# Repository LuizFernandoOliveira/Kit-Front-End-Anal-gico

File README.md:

# Kit Front-End Analógico

## Descrição
Kit didático completo de Front-End para circuitos analógicos. Este kit é perfeito para se ter na bancada, pois possui diversas funcionalidades úteis durante o desenvolvimente de sistemas microcontrolados e IoT.

---

## Descrições técnicas

- Possui LDOs de 3V3 e 5V;
- Conectores USB tipo-C e Jack para alimentação do circuito;
- Possui AmpOp Full Diferencial;
- Possui ADC Full Diferencial:
- Possui Filtro ativo de 2ª Oedem Passa-altas, Passa-baixas, Passa-faixas, Rejeita-faixas;
- Possui Filtros passivos;
- Possui Buffer;
- Possui AmpOp de instrumentação;
- Possui divisores de tensão;
- Possui resistores de Pull-Up e/ou Pull-Down;
- Possui AmpOp RRIO, Ultra-Low Power, Ultra-Low Noise Não Inversor, Inversor, Integrador, Diferenciador;
- Possui chaves analogicas;
- Possui chaves digitais;
- Possui botões e LEDS;
- Possui sensores analógicos;
- Possui diodos Schotky;
- Possui diversas tensões de referência;
- Possui diversos charge pumps.

---

## Estrutura do repositório
Os arquivos de hardware foram desenvolvidos utilizando o KiCad 9.0.
- **`.kicad_pcb`**: Layout da placa de circuito impresso (Board).
- **`.kicad_sch`**: Esquemático eletrônico do sistema (Schematic).
- **`.kicad_pro`**: Gerenciador de projeto do KiCad (Project).

---

## Autor
**Dr. Luiz Fernando Pinto de Oliveira**

*Engenheiro Eletrônico especializado em Sistemas Embarcados e Ultra-Low Power.*
- **Website:** [FAPLO](https://faplo.webnode.page/)
- **LinkedIn:** [lfpo](https://www.linkedin.com/in/lfpo/)

---

Shield: [![CC BY-NC-ND 4.0][cc-by-nc-nd-shield]][cc-by-nc-nd]

This work is licensed under a
[Creative Commons Attribution-NonCommercial-NoDerivs 4.0 International License][cc-by-nc-nd].

[![CC BY-NC-ND 4.0][cc-by-nc-nd-image]][cc-by-nc-nd]

[cc-by-nc-nd]: http://creativecommons.org/licenses/by-nc-nd/4.0/
[cc-by-nc-nd-image]: https://licensebuttons.net/l/by-nc-nd/4.0/88x31.png
[cc-by-nc-nd-shield]: https://img.shields.io/badge/License-CC%20BY--NC--ND%204.0-lightgrey.svg

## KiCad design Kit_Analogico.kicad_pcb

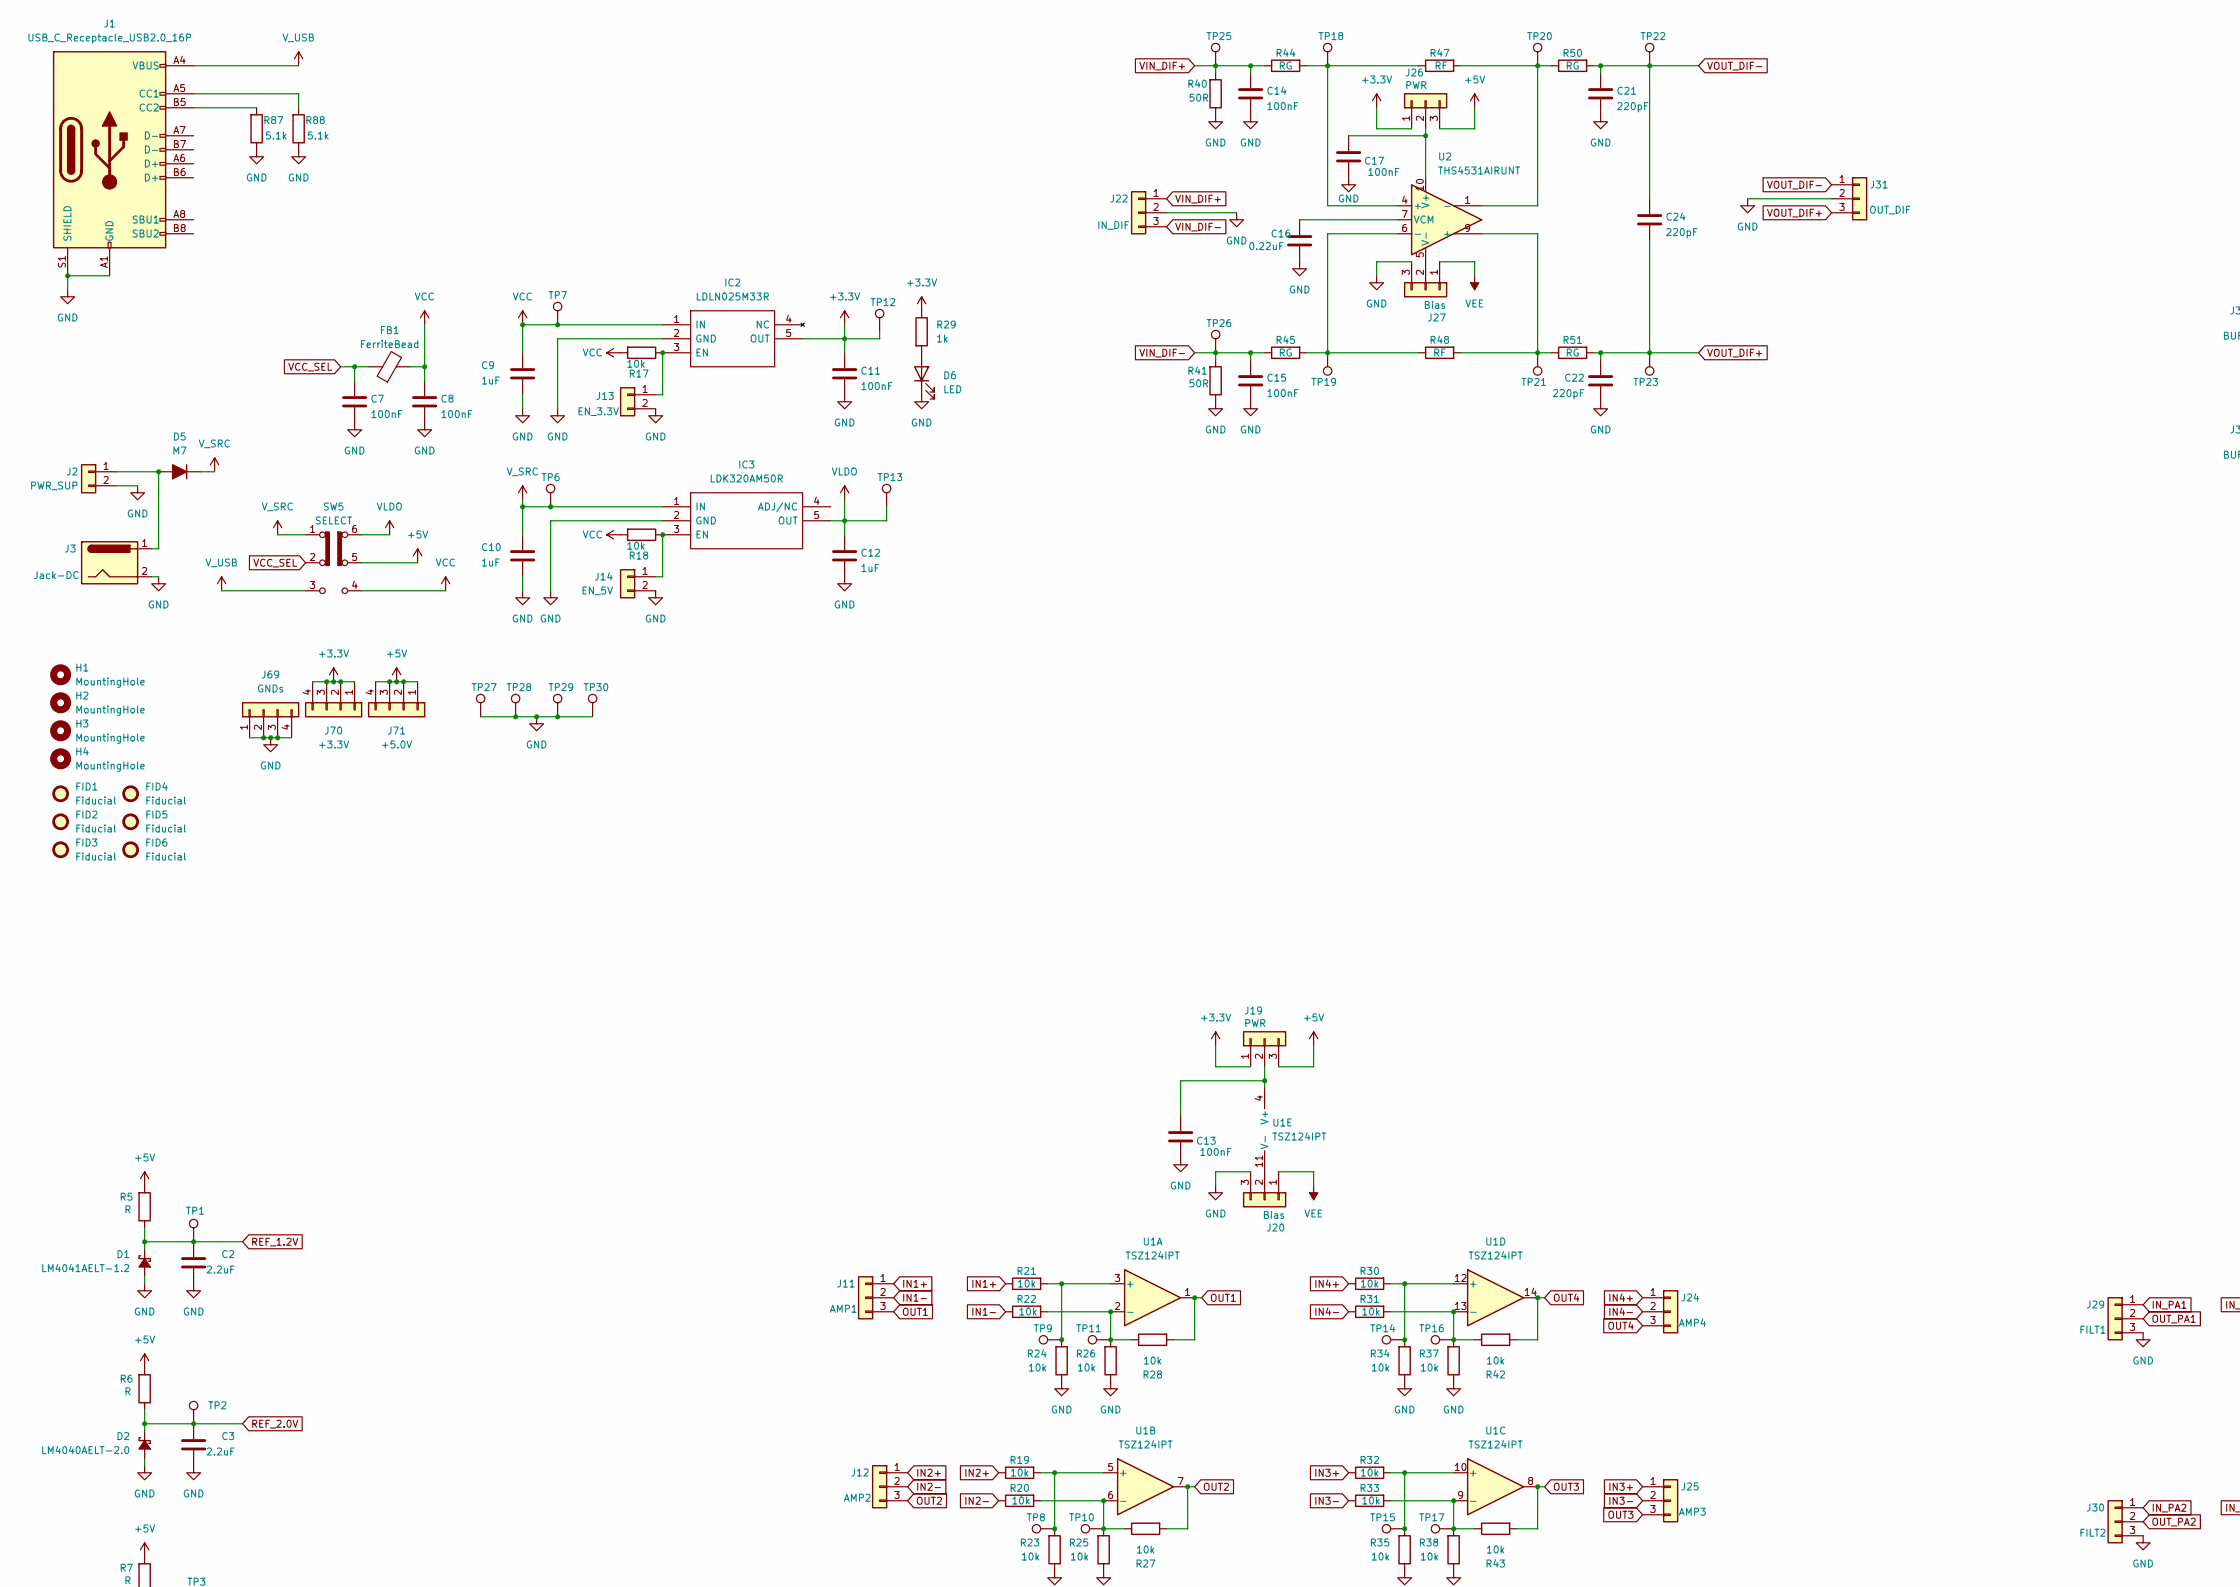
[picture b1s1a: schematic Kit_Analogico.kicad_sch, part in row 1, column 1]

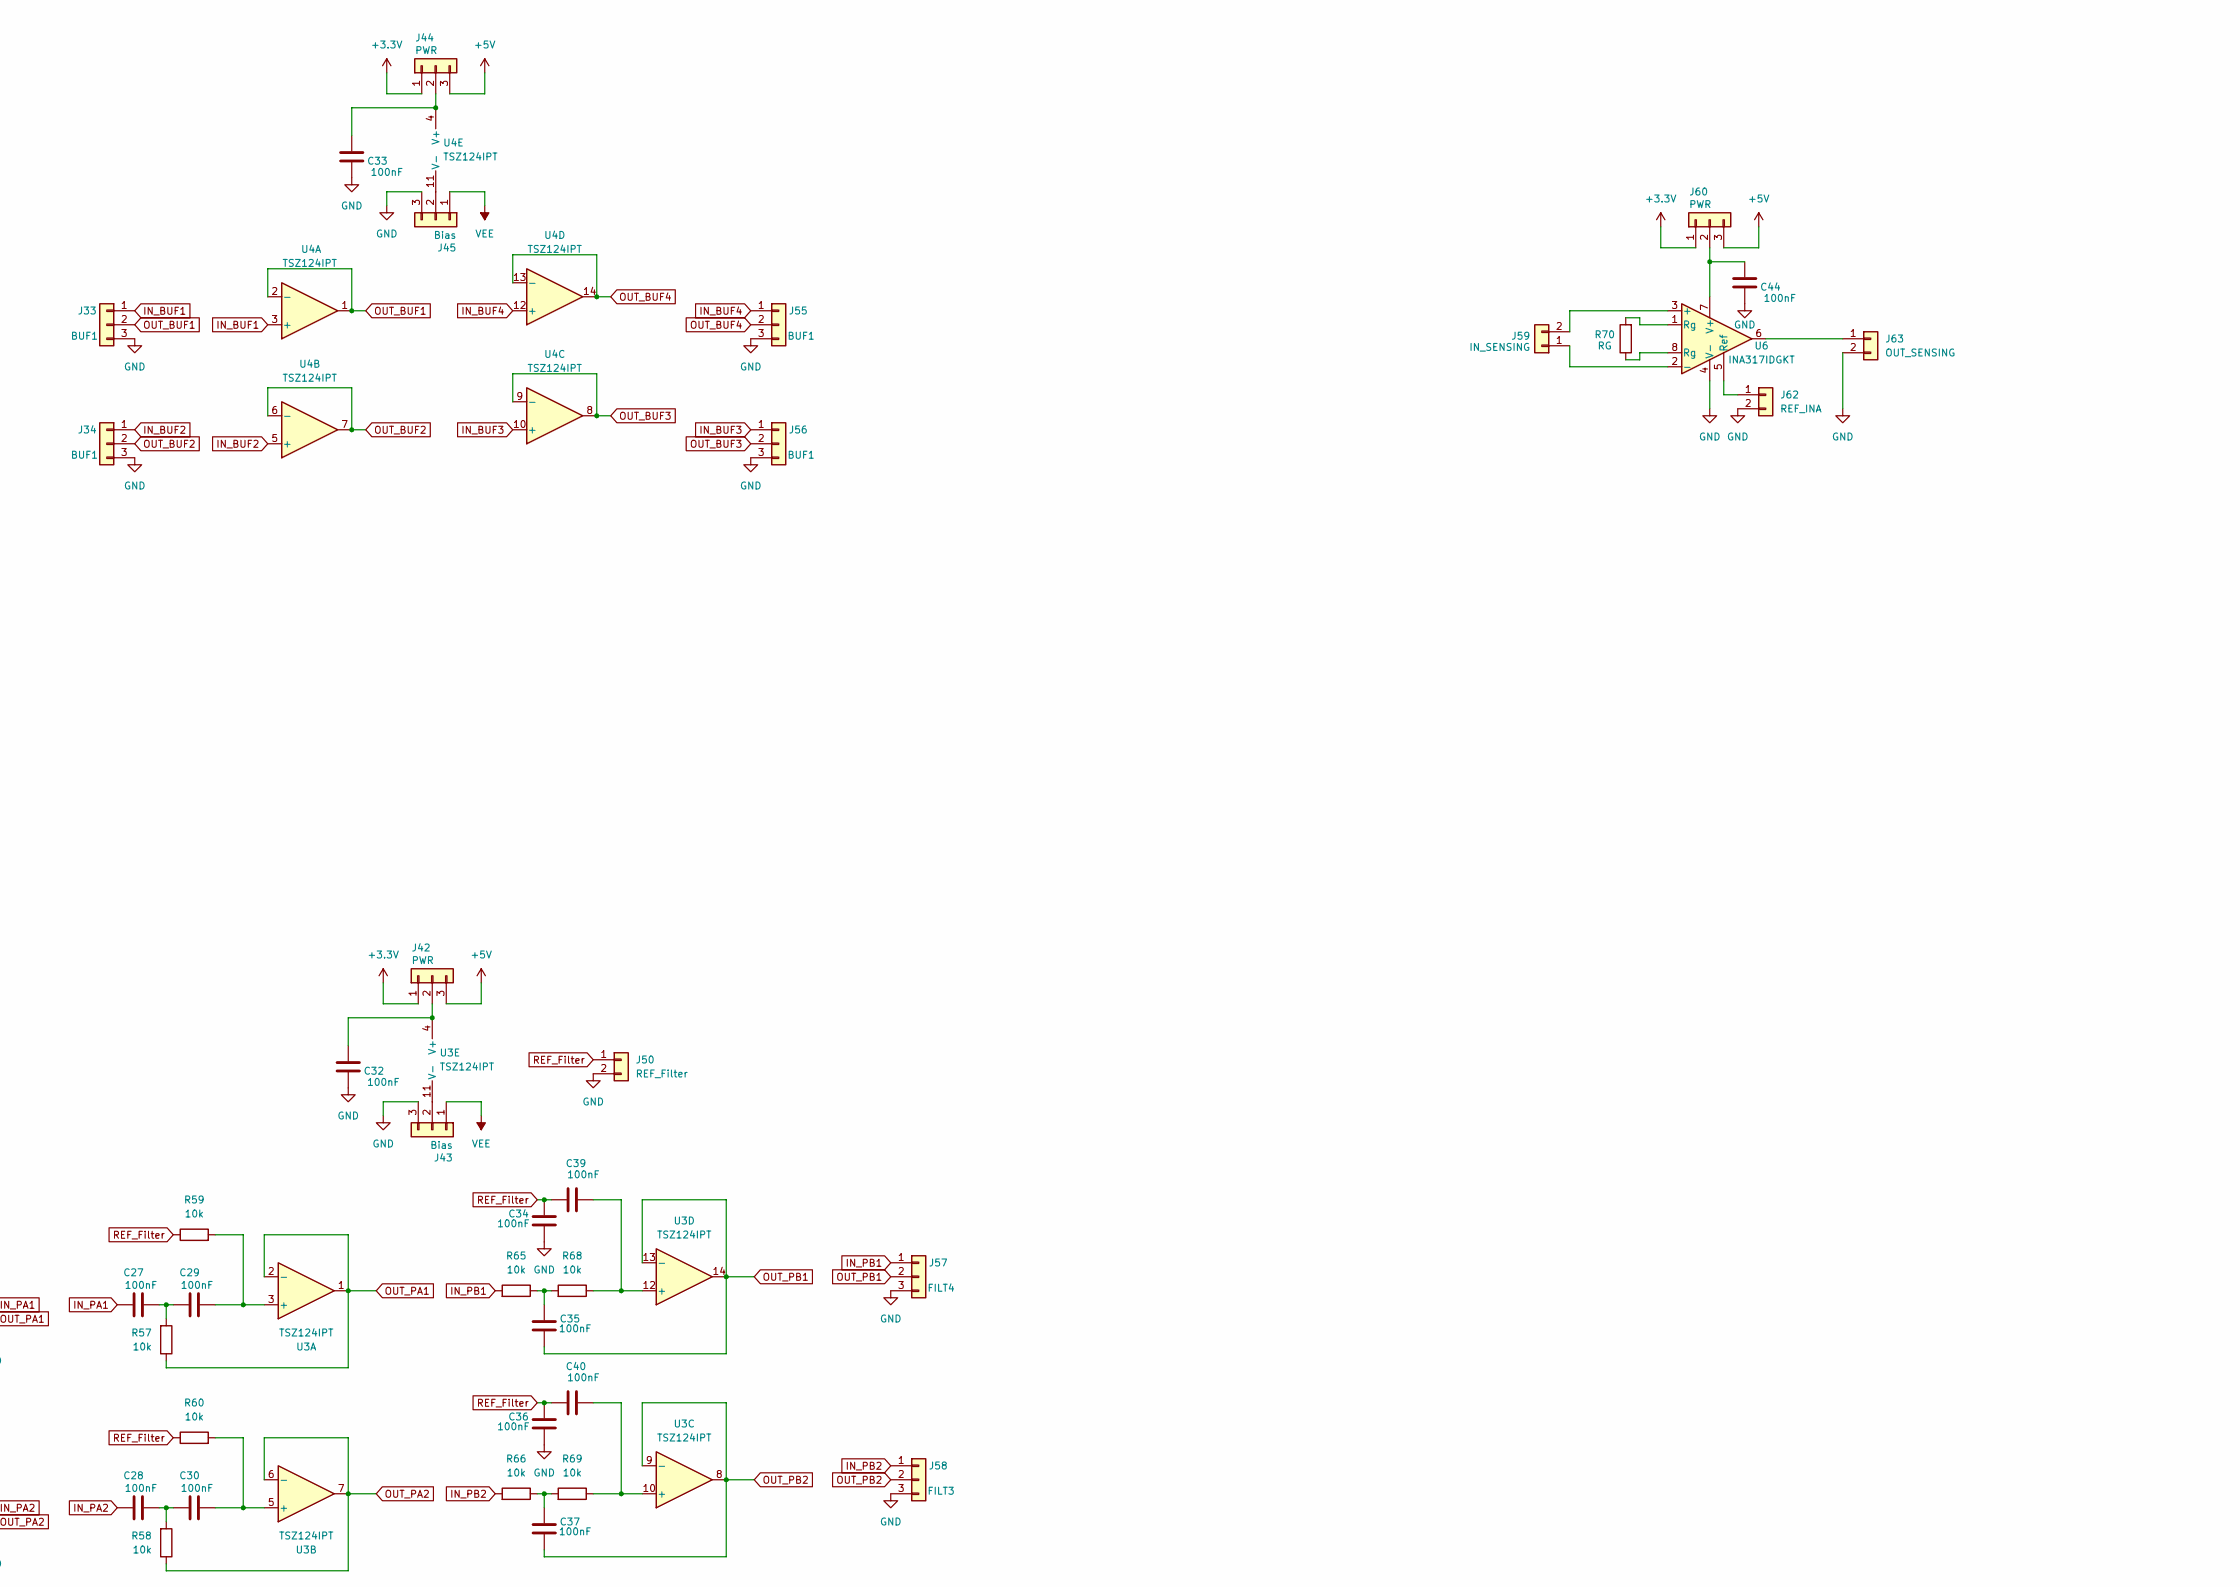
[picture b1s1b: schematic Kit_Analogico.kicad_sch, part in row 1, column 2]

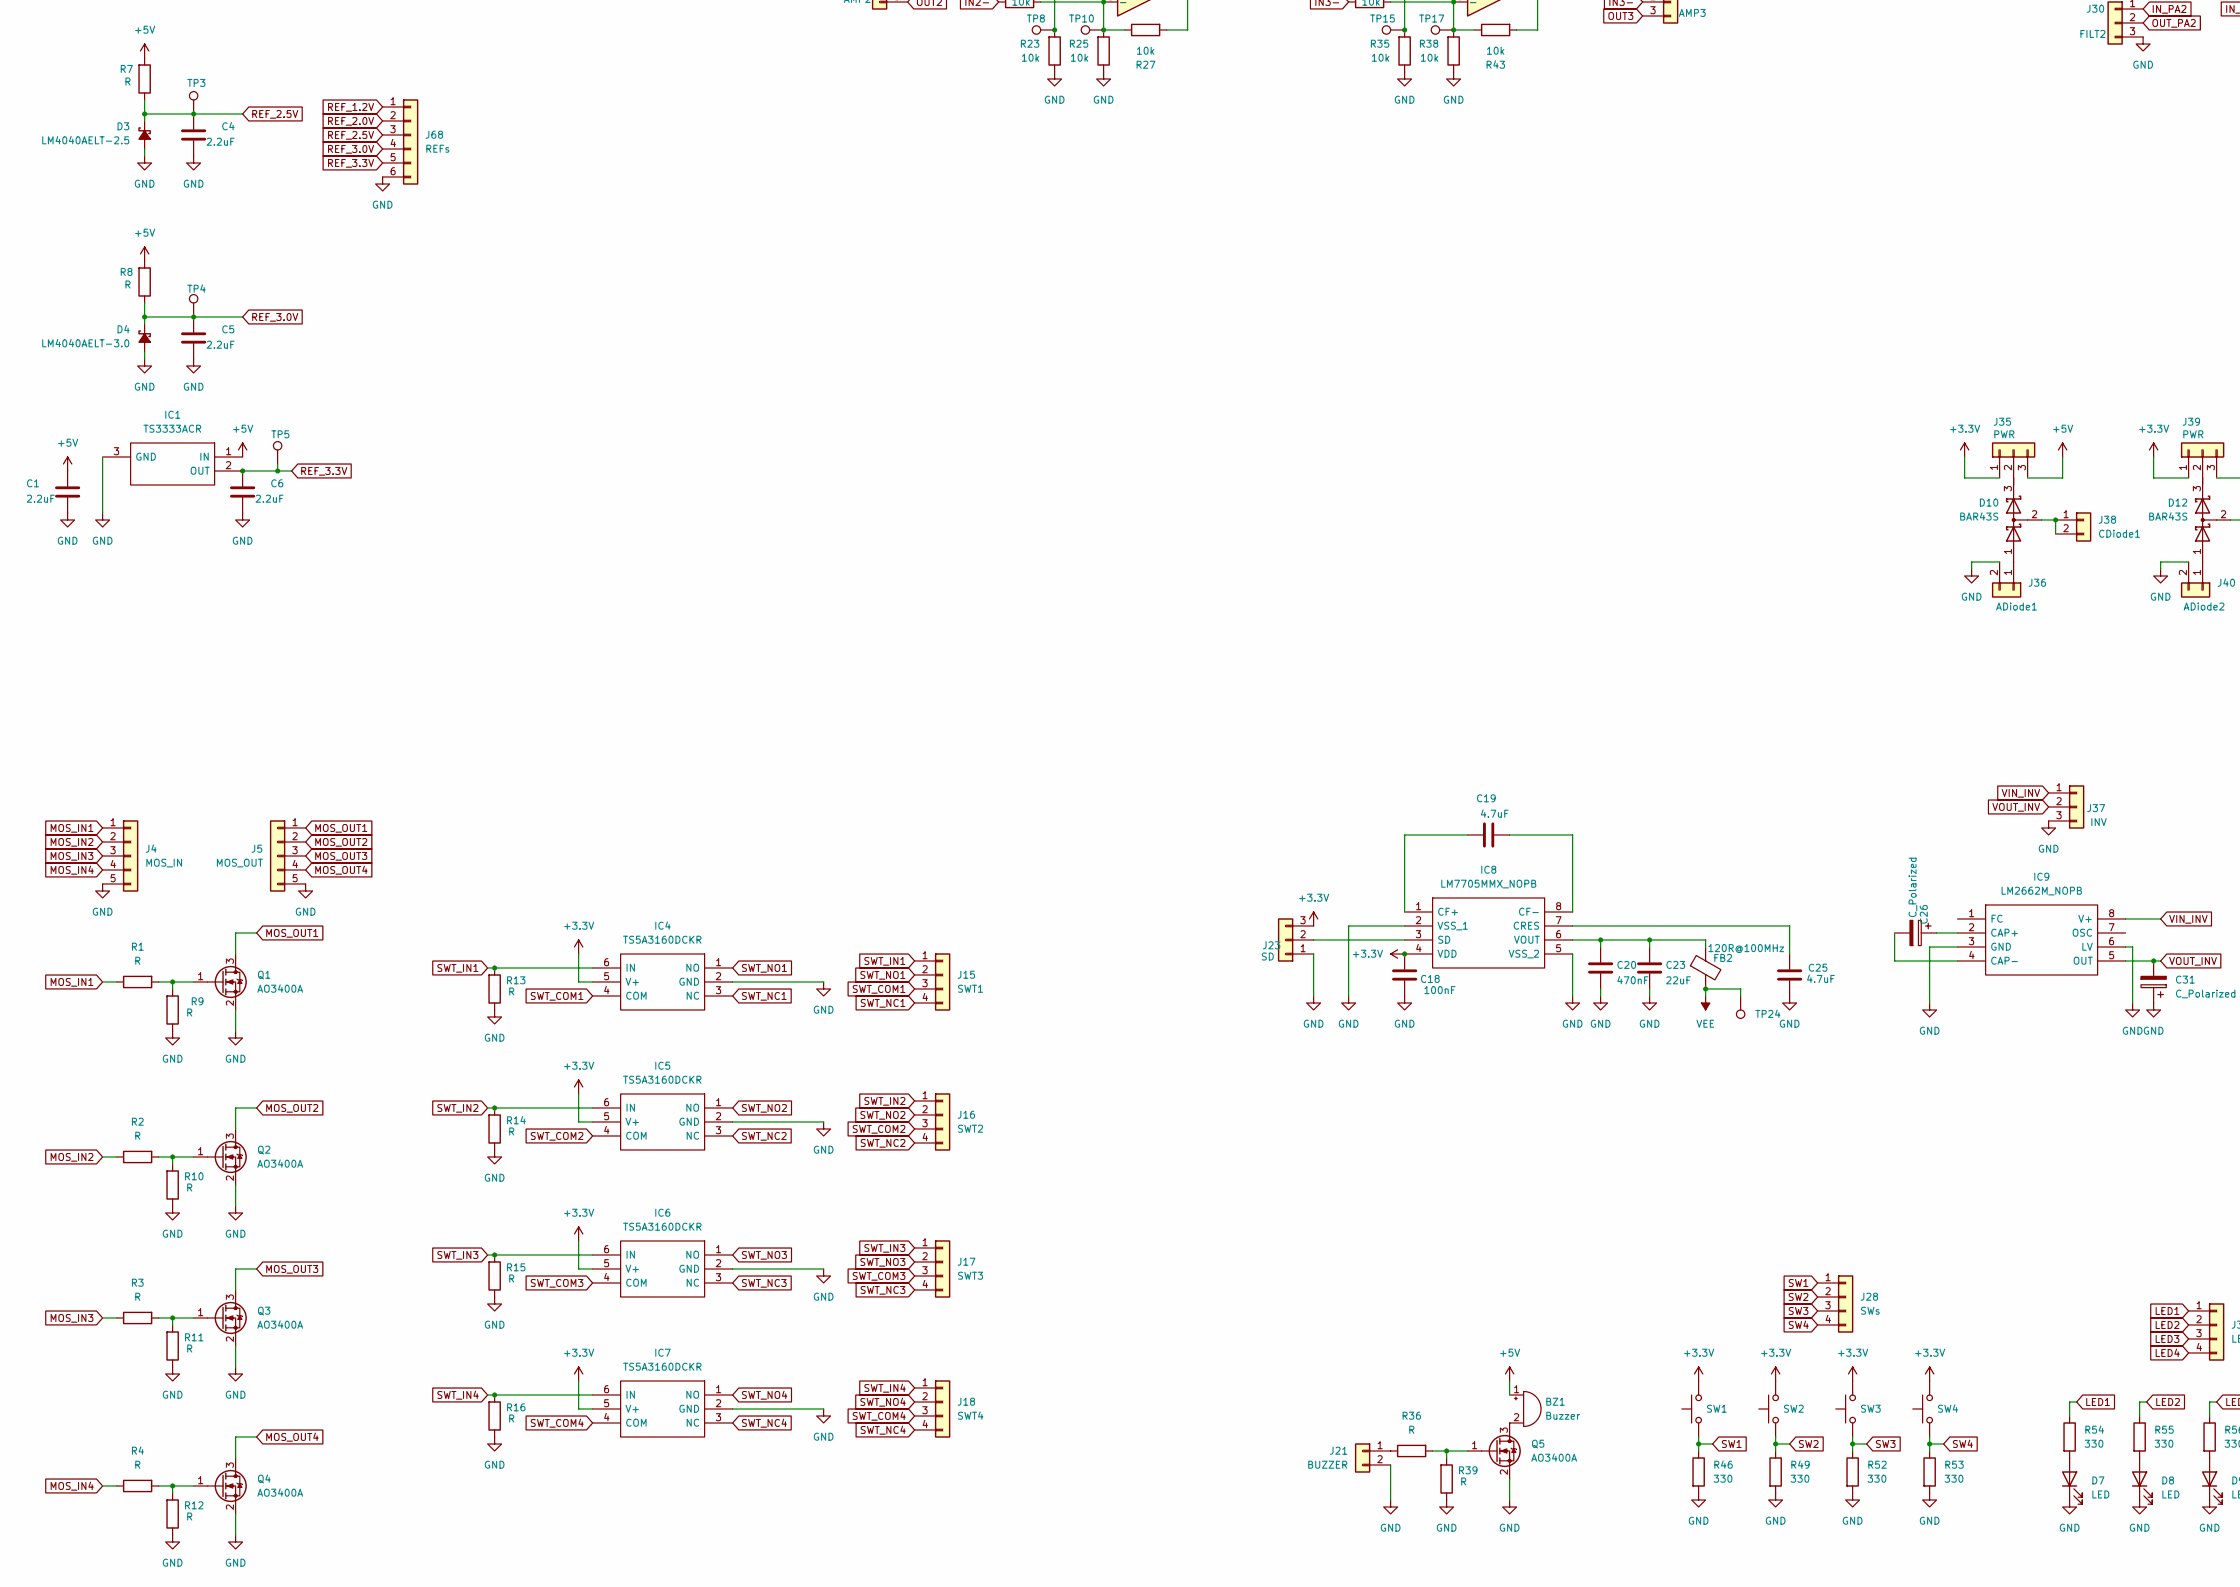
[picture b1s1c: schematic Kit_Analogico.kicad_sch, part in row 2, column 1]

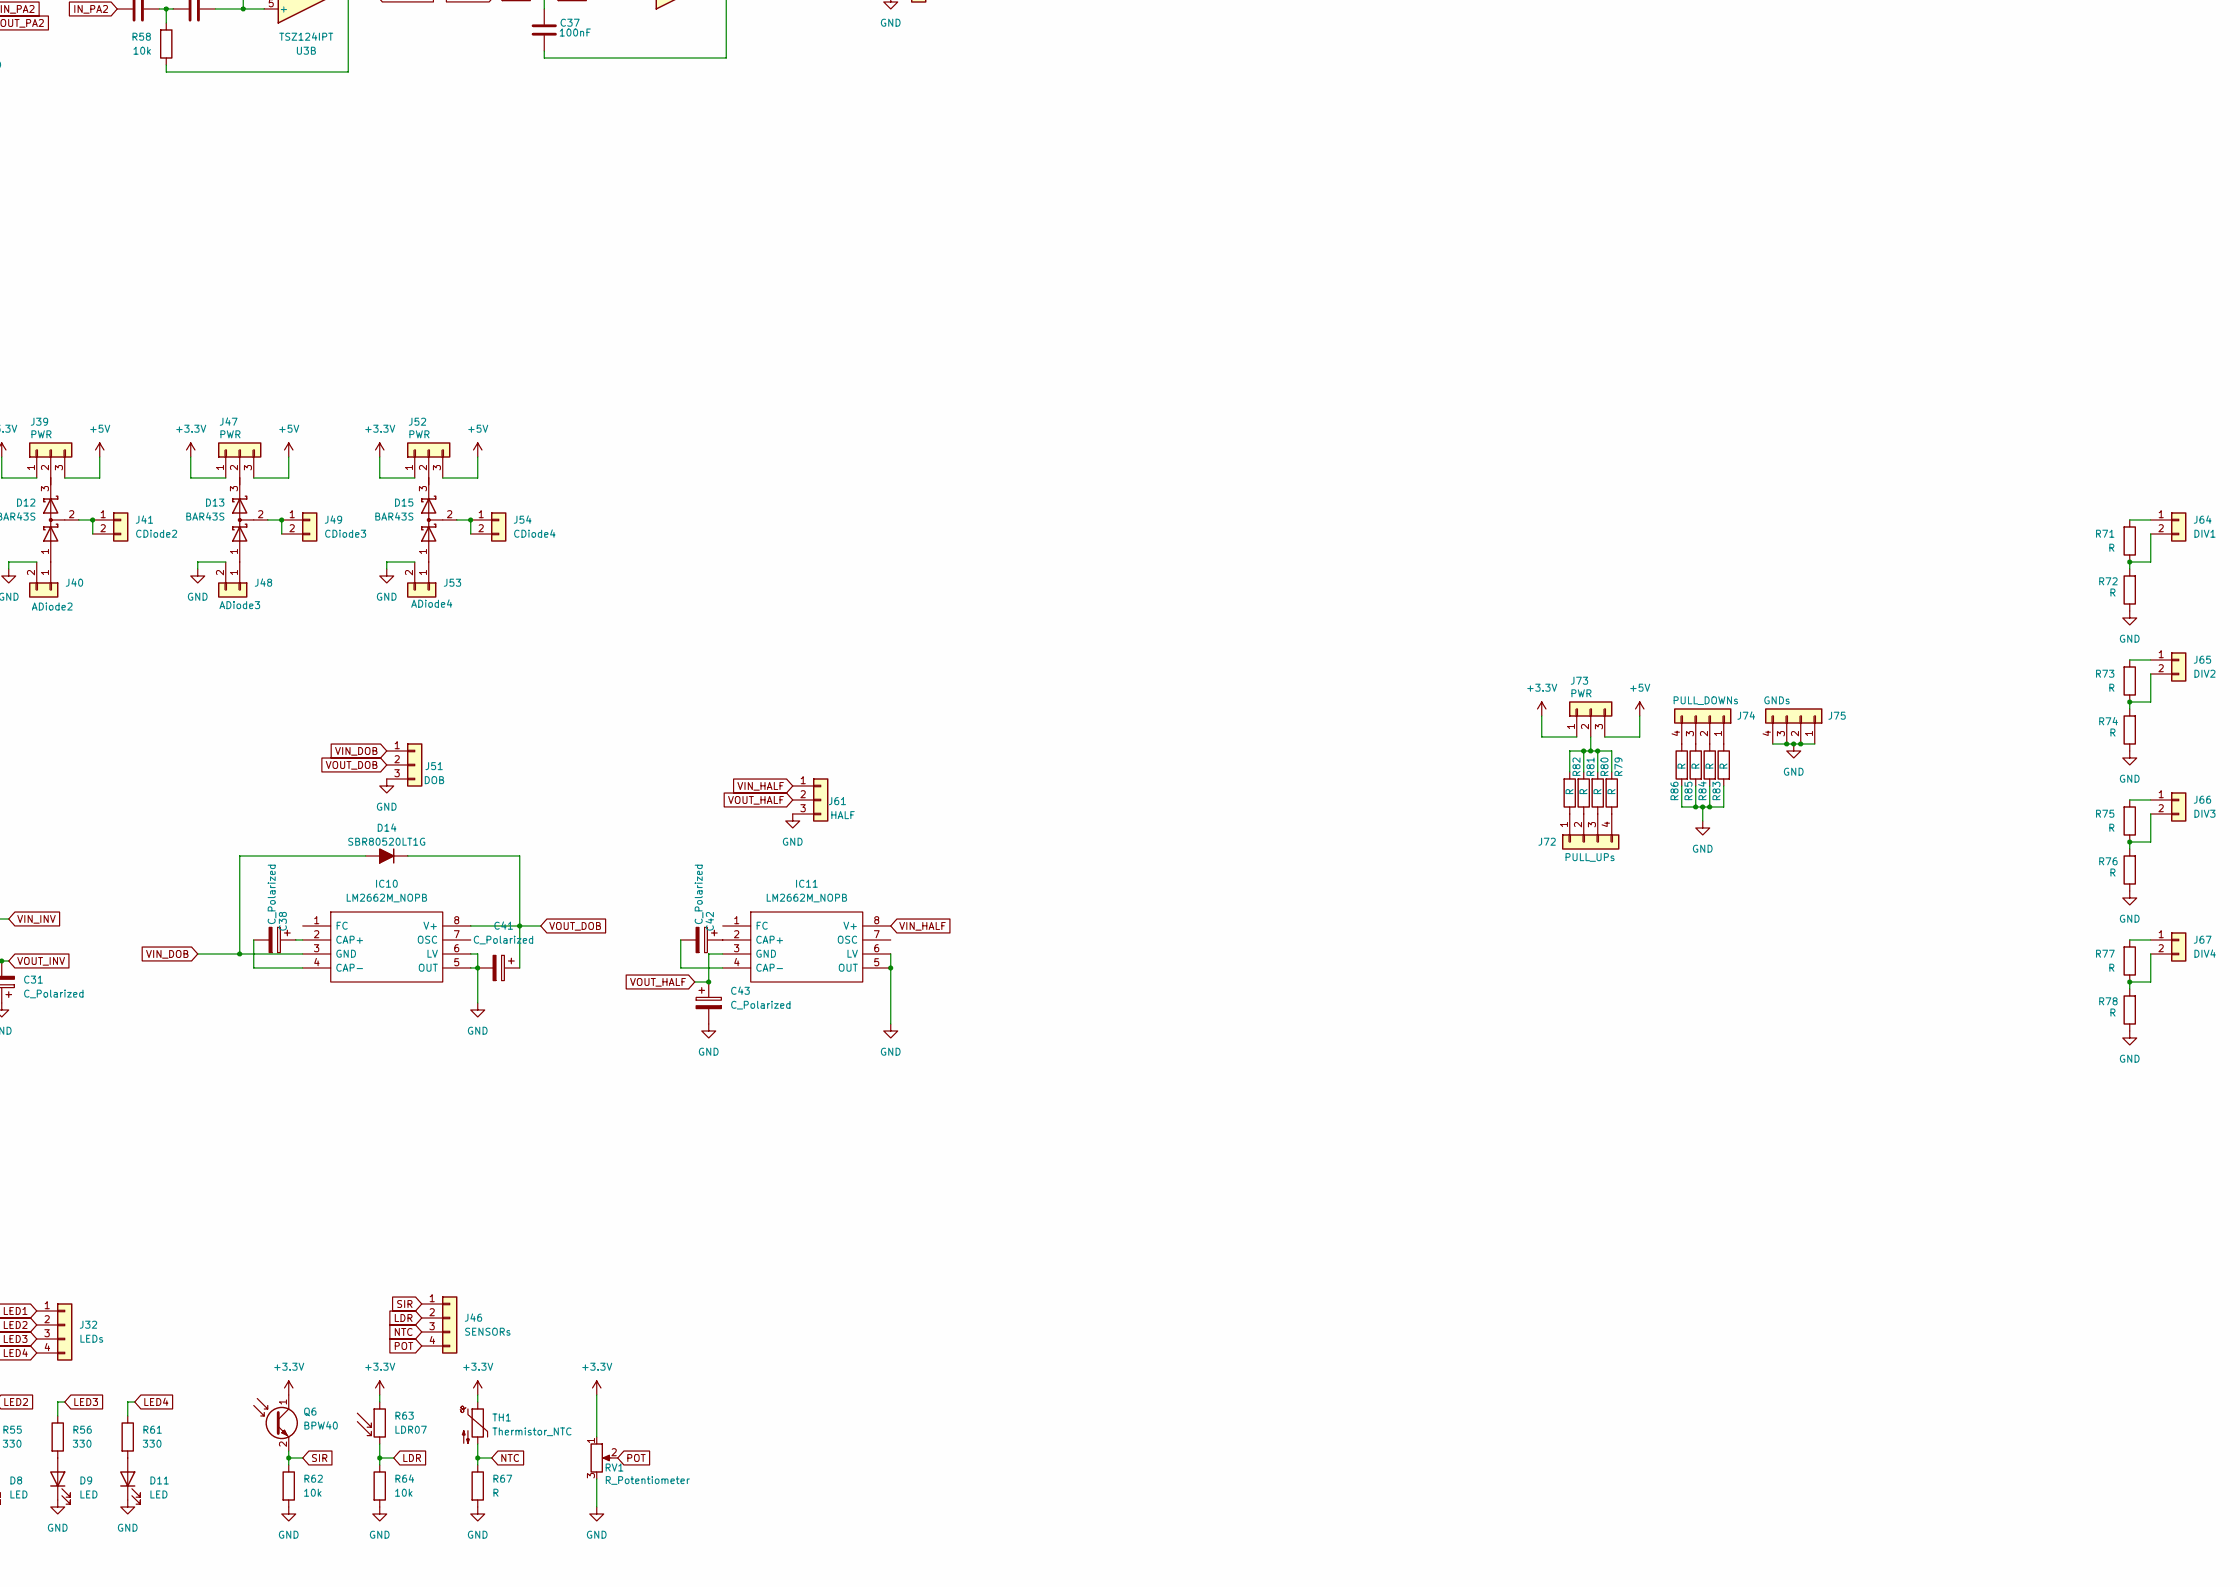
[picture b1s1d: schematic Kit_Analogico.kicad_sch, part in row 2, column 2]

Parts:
BZ1: Buzzer; Buzzer_12x9.5RM7.6
C1, C2, C3, C4, C5, C6: 2.2uF; C_0805_2012Metric
C7, C8, C11, C13, C14, C15, C17, C18, C27, C28, C29, C30, C32, C33, C34, C35, C36, C37, C39, C40, C44: 100nF; C_0805_2012Metric
C9, C10, C12: 1uF; C_0805_2012Metric
C16: 0.22uF; C_0805_2012Metric
C19, C25: 4.7uF; C_0805_2012Metric
C20: 470nF; C_0805_2012Metric
C21, C22, C24: 220pF; C_0805_2012Metric
C23: 22uF; C_0805_2012Metric
C26, C31, C38, C41, C42, C43: C_Polarized; CP_EIA-3216-10_Kemet-I_Pad1.58x1.35mm_HandSolder
D1: LM4041AELT-1.2; LM4040AELT25
D2: LM4040AELT-2.0; LM4040AELT25
D3: LM4040AELT-2.5; LM4040AELT25
D4: LM4040AELT-3.0; LM4040AELT25
D5: M7; D_SMA
D6, D7, D8, D9, D11: LED; LED_0805_2012Metric
D10, D12, D13, D15: BAR43S; SOT95P237X112-3N
D14: SBR80520LT1G; SOD3716X135N
FB1: FerriteBead; L_0805_2012Metric
FB2: 120R@100MHz; L_0805_2012Metric
FID1, FID2, FID3, FID4, FID5, FID6: Fiducial; Fiducial_1mm_Mask2mm
H1, H2, H3, H4: MountingHole; MountingHole_3.2mm_M3_DIN965
IC1: TS3333ACR; LM4040CELT20; Manufacturer_Part_Number TS3333ACR
IC2: LDLN025M33R; SOT95P280X145-5N; Manufacturer_Part_Number LDLN025M33R; Mouser Part Number 511-LDLN025M33R
IC3: LDK320AM50R; SOT95P280X145-5N; Manufacturer_Part_Number LDK320AM50R; Mouser Part Number 511-LDK320AM50R
IC4, IC5, IC6, IC7: TS5A3160DCKR; SOT65P210X110-6N; Manufacturer_Part_Number TS5A3160DCKR; Mouser Part Number 595-TS5A3160DCKR
IC8: LM7705MMX_NOPB; SOP65P490X110-8N; Manufacturer_Part_Number LM7705MMX/NOPB; Mouser Part Number 926-LM7705MMX/NOPB
IC9, IC10, IC11: LM2662M_NOPB; SOIC127P600X175-8N; Manufacturer_Part_Number LM2662M/NOPB; Mouser Part Number 926-LM2662M/NOPB
J1: USB_C_Receptacle_USB2.0_16P; USB_C_Receptacle_HRO_TYPE-C-31-M-12
J2: PWR_SUP; TerminalBlock_Altech_AK300-2_P5.00mm
J3: Jack-DC; BarrelJack_Horizontal
J4: MOS_IN; PinHeader_1x05_P2.54mm_Vertical
J5: MOS_OUT; PinHeader_1x05_P2.54mm_Vertical
J11: AMP1; PinHeader_1x03_P2.54mm_Vertical
J12: AMP2; PinHeader_1x03_P2.54mm_Vertical
J13: EN_3.3V; PinHeader_1x02_P2.54mm_Vertical
J14: EN_5V; PinHeader_1x02_P2.54mm_Vertical
J15: SWT1; PinHeader_1x04_P2.54mm_Vertical
J16: SWT2; PinHeader_1x04_P2.54mm_Vertical
J17: SWT3; PinHeader_1x04_P2.54mm_Vertical
J18: SWT4; PinHeader_1x04_P2.54mm_Vertical
J19, J26, J35, J39, J42, J44, J47, J52, J60, J73: PWR; PinHeader_1x03_P2.54mm_Vertical
J20, J27, J43, J45: Bias; PinHeader_1x03_P2.54mm_Vertical
J21: BUZZER; PinHeader_1x02_P2.54mm_Vertical
J22: IN_DIF; PinHeader_1x03_P2.54mm_Vertical
J23: SD; PinHeader_1x03_P2.54mm_Vertical
J24: AMP4; PinHeader_1x03_P2.54mm_Vertical
J25: AMP3; PinHeader_1x03_P2.54mm_Vertical
J28: SWs; PinHeader_1x04_P2.54mm_Vertical
J29: FILT1; PinHeader_1x03_P2.54mm_Vertical
J30: FILT2; PinHeader_1x03_P2.54mm_Vertical
J31: OUT_DIF; PinHeader_1x03_P2.54mm_Vertical
J32: LEDs; PinHeader_1x04_P2.54mm_Vertical
J33, J34, J55, J56: BUF1; PinHeader_1x03_P2.54mm_Vertical
J36: ADiode1; PinHeader_1x02_P2.54mm_Vertical
J37: INV; PinHeader_1x03_P2.54mm_Vertical
J38: CDiode1; PinHeader_1x02_P2.54mm_Vertical
J40: ADiode2; PinHeader_1x02_P2.54mm_Vertical
J41: CDiode2; PinHeader_1x02_P2.54mm_Vertical
J46: SENSORs; PinHeader_1x04_P2.54mm_Vertical
J48: ADiode3; PinHeader_1x02_P2.54mm_Vertical
J49: CDiode3; PinHeader_1x02_P2.54mm_Vertical
J50: REF_Filter; PinHeader_1x02_P2.54mm_Vertical
J51: DOB; PinHeader_1x03_P2.54mm_Vertical
J53: ADiode4; PinHeader_1x02_P2.54mm_Vertical
J54: CDiode4; PinHeader_1x02_P2.54mm_Vertical
J57: FILT4; PinHeader_1x03_P2.54mm_Vertical
J58: FILT3; PinHeader_1x03_P2.54mm_Vertical
J59: IN_SENSING; PinHeader_1x02_P2.54mm_Vertical
J61: HALF; PinHeader_1x03_P2.54mm_Vertical
J62: REF_INA; PinHeader_1x02_P2.54mm_Vertical
J63: OUT_SENSING; PinHeader_1x02_P2.54mm_Vertical
J64: DIV1; PinHeader_1x02_P2.54mm_Vertical
J65: DIV2; PinHeader_1x02_P2.54mm_Vertical
J66: DIV3; PinHeader_1x02_P2.54mm_Vertical
J67: DIV4; PinHeader_1x02_P2.54mm_Vertical
J68: REFs; PinHeader_1x06_P2.54mm_Vertical
J69, J75: GNDs; PinHeader_1x04_P2.54mm_Vertical
J70: +3.3V; PinHeader_1x04_P2.54mm_Vertical
J71: +5.0V; PinHeader_1x04_P2.54mm_Vertical
J72: PULL_UPs; PinHeader_1x04_P2.54mm_Vertical
J74: PULL_DOWNs; PinHeader_1x04_P2.54mm_Vertical
Q1, Q2, Q3, Q4, Q5: AO3400A; SOT-23
Q6: BPW40; LED_D5.0mm_Clear
R1, R2, R3, R4, R5, R6, R7, R8, R9, R10, R11, R12, R13, R14, R15, R16, R36, R39, R67, R71, R72, R73, R74, R75, R76, R77, R78, R79, R80, R81, R82, R83, R84, R85, R86: R; R_0805_2012Metric
R17, R18, R19, R20, R21, R22, R23, R24, R25, R26, R27, R28, R30, R31, R32, R33, R34, R35, R37, R38, R42, R43, R57, R58, R59, R60, R62, R64, R65, R66, R68, R69: 10k; R_0805_2012Metric
R29: 1k; R_0805_2012Metric
R40, R41: 50R; R_0805_2012Metric
R44, R45, R50, R51, R70: RG; R_0805_2012Metric
R46, R49, R52, R53, R54, R55, R56, R61: 330; R_0805_2012Metric
R47, R48: RF; R_0805_2012Metric
R63: LDR07; R_LDR_5.1x4.3mm_P3.4mm_Vertical
R87, R88: 5.1k; R_0805_2012Metric
RV1: R_Potentiometer; RM065503
SW1, SW2, SW3, SW4: SW_Push; SW_PUSH_6mm_H5mm
SW5: SELECT; SW_E-Switch_EG1271_SPDT
TH1: Thermistor_NTC; PinHeader_1x02_P2.54mm_Vertical
TP1, TP2, TP3, TP4, TP5, TP6, TP7, TP8, TP9, TP10, TP11, TP12, TP13, TP14, TP15, TP16, TP17, TP18, TP19, TP20, TP21, TP22, TP23, TP24, TP25, TP26, TP27, TP28, TP29, TP30: TestPoint; TestPoint_Loop_D1.80mm_Drill1.0mm_Beaded
U1, U3, U4: TSZ124IPT; SOP65P640X120-14N
U2: THS4531AIRUNT; QFN50P200X200X80-10N-D
U6: INA317IDGKT; SOP65P490X110-8N

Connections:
+3.3V: C11.1, C18.2, IC2.5 (OUT), IC4.5 (V+), IC5.5 (V+), IC6.5 (V+), IC7.5 (V+), IC8.4 (VDD), J19.1, J23.3, J26.1, J35.1, J39.1, J42.1, J44.1, J47.1, J52.1, J60.1, J70.1, J70.2, J70.3, J70.4, J73.1, Q6.1 (C), R29.1, R63.1, RV1.1, SW1.2, SW2.2, SW3.2, SW4.2, TH1.1, TP12.1
+5V: BZ1.1 (+), C1.1, IC1.1 (IN), J19.3, J26.3, J35.3, J39.3, J42.3, J44.3, J47.3, J52.3, J60.3, J71.1, J71.2, J71.3, J71.4, J73.3, R5.2, R6.2, R7.2, R8.2, SW5.5 (B)
GND: C1.2, C2.2, C3.2, C4.2, C5.2, C6.2, C7.2, C8.2, C9.2, C10.2, C11.2, C12.2, C13.1, C14.2, C15.2, C16.2, C17.1, C18.1, C20.2, C21.2, C22.2, C23.2, C25.1, C31.1, C32.1, C33.1, C34.1, C36.1, C41.2, C43.2, C44.1, D1.2 (A), D2.2 (A), D3.2 (A), D4.2 (A), D6.1 (K), D7.1 (K), D8.1 (K), D9.1 (K), D11.1 (K), IC1.3 (GND), IC2.2 (GND), IC3.2 (GND), IC4.2 (GND), IC5.2 (GND), IC6.2 (GND), IC7.2 (GND), IC8.2 (VSS_1), IC8.5 (VSS_2), IC9.3 (GND), IC9.6 (LV), IC10.5 (OUT), IC10.6 (LV), IC11.5 (OUT), IC11.6 (LV), J1.A1 (GND), J1.A12 (GND), J1.B1 (GND), J1.B12 (GND), J1.S1 (SHIELD), J2.2, J3.2, J4.5, J5.5, J13.2, J14.2, J20.3, J21.2, J22.2, J23.1, J27.3, J29.3, J30.3, J31.2, J33.3, J34.3, J36.2, J37.3, J40.2, J43.3, J45.3, J48.2, J50.2, J51.3, J53.2, J55.3, J56.3, J57.3, J58.3, J61.3, J62.2, J63.2, J68.6, J69.1, J69.2, J69.3, J69.4, J75.1, J75.2, J75.3, J75.4, Q1.2 (S), Q2.2 (S), Q3.2 (S), Q4.2 (S), Q5.2 (S), R9.1, R10.1, R11.1, R12.1, R13.1, R14.1, R15.1, R16.1, R23.1, R24.1, R25.1, R26.1, R34.1, R35.1, R37.1, R38.1, R39.1, R40.1, R41.1, R46.2, R49.2, R52.2, R53.2, R62.2, R64.2, R67.2, R72.1, R74.1, R76.1, R78.1, R83.2, R84.2, R85.2, R86.2, R87.1, R88.1, RV1.3, TP27.1, TP28.1, TP29.1, TP30.1, U6.4 (V-)
IN1+: J11.1, R21.1
IN1-: J11.2, R22.1
IN2+: J12.1, R19.1
IN2-: J12.2, R20.1
IN3+: J25.1, R32.1
IN3-: J25.2, R33.1
IN4+: J24.1, R30.1
IN4-: J24.2, R31.1
IN_BUF1: J33.1, U4.3 (+)
IN_BUF2: J34.1, U4.5 (+)
IN_BUF3: J56.1, U4.10 (+)
IN_BUF4: J55.1, U4.12 (+)
IN_PA1: C27.2, J29.1
IN_PA2: C28.2, J30.1
IN_PB1: J57.1, R65.2
IN_PB2: J58.1, R66.2
LDR: J46.2, R63.2, R64.1
LED1: J32.1, R54.1
LED2: J32.2, R55.1
LED3: J32.3, R56.1
LED4: J32.4, R61.1
MOS_IN1: J4.1, R1.1
MOS_IN2: J4.2, R2.1
MOS_IN3: J4.3, R3.1
MOS_IN4: J4.4, R4.1
MOS_OUT1: J5.1, Q1.3 (D)
MOS_OUT2: J5.2, Q2.3 (D)
MOS_OUT3: J5.3, Q3.3 (D)
MOS_OUT4: J5.4, Q4.3 (D)
NTC: J46.3, R67.1, TH1.2
unnamed: BZ1.2 (-), Q5.3 (D)
unnamed: C27.1, C29.2, R57.2
unnamed: C28.1, C30.2, R58.2
unnamed: C35.2, R65.1, R68.2
unnamed: C37.2, R66.1, R69.2
unnamed: D5.2 (A), J2.1, J3.1
unnamed: D6.2 (A), R29.2
unnamed: D7.2 (A), R54.2
unnamed: D8.2 (A), R55.2
unnamed: D9.2 (A), R56.2
unnamed: D10.1 (A), J36.1
unnamed: D10.3 (K), J35.2
unnamed: D10.2 (common), J38.1, J38.2
unnamed: D11.2 (A), R61.2
unnamed: D12.1 (A), J40.1
unnamed: D12.3 (K), J39.2
unnamed: D12.2 (common), J41.1, J41.2
unnamed: D13.1 (A), J48.1
unnamed: D13.3 (K), J47.2
unnamed: D13.2 (common), J49.1, J49.2
unnamed: D15.1 (A), J53.1
unnamed: D15.3 (K), J52.2
unnamed: D15.2 (common), J54.1, J54.2
unnamed: IC2.3 (EN), J13.1, R17.1
unnamed: IC3.3 (EN), J14.1, R18.1
unnamed: C19.1, IC8.1 (CF+)
unnamed: C19.2, IC8.8 (CF-)
unnamed: C25.2, IC8.7 (CRES)
unnamed: IC8.3 (SD), J23.2
unnamed: C20.1, C23.1, FB2.1, IC8.6 (VOUT)
unnamed: C26.1, IC9.2 (CAP+)
unnamed: C26.2, IC9.4 (CAP-)
unnamed: C38.1, IC10.2 (CAP+)
unnamed: C38.2, IC10.4 (CAP-)
unnamed: C42.1, IC11.2 (CAP+)
unnamed: C42.2, IC11.4 (CAP-)
unnamed: J1.A5 (CC1), R88.2
unnamed: J1.B5 (CC2), R87.2
unnamed: C13.2, J19.2, U1.4 (V+)
unnamed: J20.2, U1.11 (V-)
unnamed: J21.1, R36.1
unnamed: C17.2, J26.2, U2.10 (V+)
unnamed: J27.2, U2.5 (V-)
unnamed: C32.2, J42.2, U3.4 (V+)
unnamed: J43.2, U3.11 (V-)
unnamed: C33.2, J44.2, U4.4 (V+)
unnamed: J45.2, U4.11 (V-)
unnamed: J59.1, U6.2 (-)
unnamed: J59.2, U6.3 (+)
unnamed: C44.2, J60.2, U6.7 (V+)
unnamed: J62.1, U6.5 (Ref)
unnamed: J63.1, U6.6
unnamed: J64.1, R71.2
unnamed: J64.2, R71.1, R72.2
unnamed: J65.1, R73.2
unnamed: J65.2, R73.1, R74.2
unnamed: J66.1, R75.2
unnamed: J66.2, R75.1, R76.2
unnamed: J67.1, R77.2
unnamed: J67.2, R77.1, R78.2
unnamed: J72.1, R82.1
unnamed: J72.2, R81.1
unnamed: J72.3, R80.1
unnamed: J72.4, R79.1
unnamed: J73.2, R79.2, R80.2, R81.2, R82.2
unnamed: J74.1, R83.1
unnamed: J74.2, R84.1
unnamed: J74.3, R85.1
unnamed: J74.4, R86.1
unnamed: Q1.1 (G), R1.2, R9.2
unnamed: Q2.1 (G), R2.2, R10.2
unnamed: Q3.1 (G), R3.2, R11.2
unnamed: Q4.1 (G), R4.2, R12.2
unnamed: Q5.1 (G), R36.2, R39.2
unnamed: R44.2, R47.1, TP18.1, U2.4 (+)
unnamed: R45.2, R48.1, TP19.1, U2.6 (-)
unnamed: R47.2, R50.1, TP20.1, U2.1 (-)
unnamed: R48.2, R51.1, TP21.1, U2.9 (+)
unnamed: R70.1, U6.8 (Rg)
unnamed: R70.2, U6.1 (Rg)
unnamed: R21.2, R24.2, TP9.1, U1.3 (+)
unnamed: R22.2, R26.2, R28.1, TP11.1, U1.2 (-)
unnamed: R19.2, R23.2, TP8.1, U1.5 (+)
unnamed: R20.2, R25.2, R27.1, TP10.1, U1.6 (-)
unnamed: R32.2, R35.2, TP15.1, U1.10 (+)
unnamed: R33.2, R38.2, R43.1, TP17.1, U1.9 (-)
unnamed: R30.2, R34.2, TP14.1, U1.12 (+)
unnamed: R31.2, R37.2, R42.1, TP16.1, U1.13 (-)
unnamed: C16.1, U2.7 (VCM)
unnamed: C29.1, R59.2, U3.3 (+)
unnamed: C30.1, R60.2, U3.5 (+)
unnamed: C40.1, R69.1, U3.10 (+)
unnamed: C39.1, R68.1, U3.12 (+)
OUT1: J11.3, R28.2, U1.1
OUT2: J12.3, R27.2, U1.7
OUT3: J25.3, R43.2, U1.8
OUT4: J24.3, R42.2, U1.14
OUT_BUF1: J33.2, U4.1, U4.2 (-)
OUT_BUF2: J34.2, U4.6 (-), U4.7
OUT_BUF3: J56.2, U4.8, U4.9 (-)
OUT_BUF4: J55.2, U4.13 (-), U4.14
OUT_PA1: J29.2, R57.1, U3.1, U3.2 (-)
OUT_PA2: J30.2, R58.1, U3.6 (-), U3.7
OUT_PB1: C35.1, J57.2, U3.13 (-), U3.14
OUT_PB2: C37.1, J58.2, U3.8, U3.9 (-)
POT: J46.4, RV1.2
REF_1.2V: C2.1, D1.1 (K), J68.1, R5.1, TP1.1
REF_2.0V: C3.1, D2.1 (K), J68.2, R6.1, TP2.1
REF_2.5V: C4.1, D3.1 (K), J68.3, R7.1, TP3.1
REF_3.0V: C5.1, D4.1 (K), J68.4, R8.1, TP4.1
REF_3.3V: C6.1, IC1.2 (OUT), J68.5, TP5.1
REF_Filter: C34.2, C36.2, C39.2, C40.2, J50.1, R59.1, R60.1
SIR: J46.1, Q6.2 (E), R62.1
SW1: J28.1, R46.1, SW1.1
SW2: J28.2, R49.1, SW2.1
SW3: J28.3, R52.1, SW3.1
SW4: J28.4, R53.1, SW4.1
SWT_COM1: IC4.4 (COM), J15.3
SWT_COM2: IC5.4 (COM), J16.3
SWT_COM3: IC6.4 (COM), J17.3
SWT_COM4: IC7.4 (COM), J18.3
SWT_IN1: IC4.6 (IN), J15.1, R13.2
SWT_IN2: IC5.6 (IN), J16.1, R14.2
SWT_IN3: IC6.6 (IN), J17.1, R15.2
SWT_IN4: IC7.6 (IN), J18.1, R16.2
SWT_NC1: IC4.3 (NC), J15.4
SWT_NC2: IC5.3 (NC), J16.4
SWT_NC3: IC6.3 (NC), J17.4
SWT_NC4: IC7.3 (NC), J18.4
SWT_NO1: IC4.1 (NO), J15.2
SWT_NO2: IC5.1 (NO), J16.2
SWT_NO3: IC6.1 (NO), J17.2
SWT_NO4: IC7.1 (NO), J18.2
VCC: C8.1, C9.1, FB1.2, IC2.1 (IN), R17.2, R18.2, SW5.4 (A), TP7.1
VCC_SEL: C7.1, FB1.1, SW5.2 (B)
VEE: FB2.2, J20.1, J27.1, J43.1, J45.1, TP24.1
VIN_DIF+: C14.1, J22.1, R40.2, R44.1, TP25.1
VIN_DIF-: C15.1, J22.3, R41.2, R45.1, TP26.1
VIN_DOB: D14.2 (A), IC10.3 (GND), J51.1
VIN_HALF: IC11.8 (V+), J61.1
VIN_INV: IC9.8 (V+), J37.1
VLDO: C12.1, IC3.5 (OUT), SW5.6 (C), TP13.1
VOUT_DIF+: C22.1, C24.2, J31.3, R51.2, TP23.1
VOUT_DIF-: C21.1, C24.1, J31.1, R50.2, TP22.1
VOUT_DOB: C41.1, D14.1 (K), IC10.8 (V+), J51.2
VOUT_HALF: C43.1, IC11.3 (GND), J61.2
VOUT_INV: C31.2, IC9.5 (OUT), J37.2
V_SRC: C10.1, D5.1 (K), IC3.1 (IN), SW5.1 (A), TP6.1
V_USB: J1.A4 (VBUS), J1.A9 (VBUS), J1.B4 (VBUS), J1.B9 (VBUS), SW5.3 (C)
